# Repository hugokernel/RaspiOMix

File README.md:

RaspiOMix
=========

A RaspberryPi board with 5V tolerance and Grove compatible.

Specifications
--------------

- 4 general 5V tolerant input / output
- 4 analog input, 0-5V, 18 bit resolution (MCP3424)
- 2 digital input via DIP switch
- Real Time Clock with battery backup (DS1307)
- 2 I2C external connector
- 1 serial external connector
- Power input via jack

Python example :

    >>> from raspiomix import Raspiomix
    >>> r = Raspiomix()
    >>> r.readRtc()
    2014-11-12T20:41:26
    >>> print(r.readAdc(0))
    [4.0669732000000005]
    >>>print(r.readAdc((0, 1, 2, 3)))
    [4.066934600000001, 0.010923800000000001, 0.08515160000000001, 0.2866822]

--

Une carte fille pour RaspberryPi avec entrées / sorties tolérantes au 5V et des connecteurs compatible Grove.

Caractéristiques
----------------

- 4 entrées / sorties tolérantes 5V
- 4 entrées analogiques, 0-5V, 18 bits de résolution (MCP3424)
- 2 entrées numériques via DIP switch
- Horloge temps réel avec batterie de sauvegarde (DS1307)
- 2 connecteurs pour I2C
- 1 connecteur pour communication série
- Alimentation via jack

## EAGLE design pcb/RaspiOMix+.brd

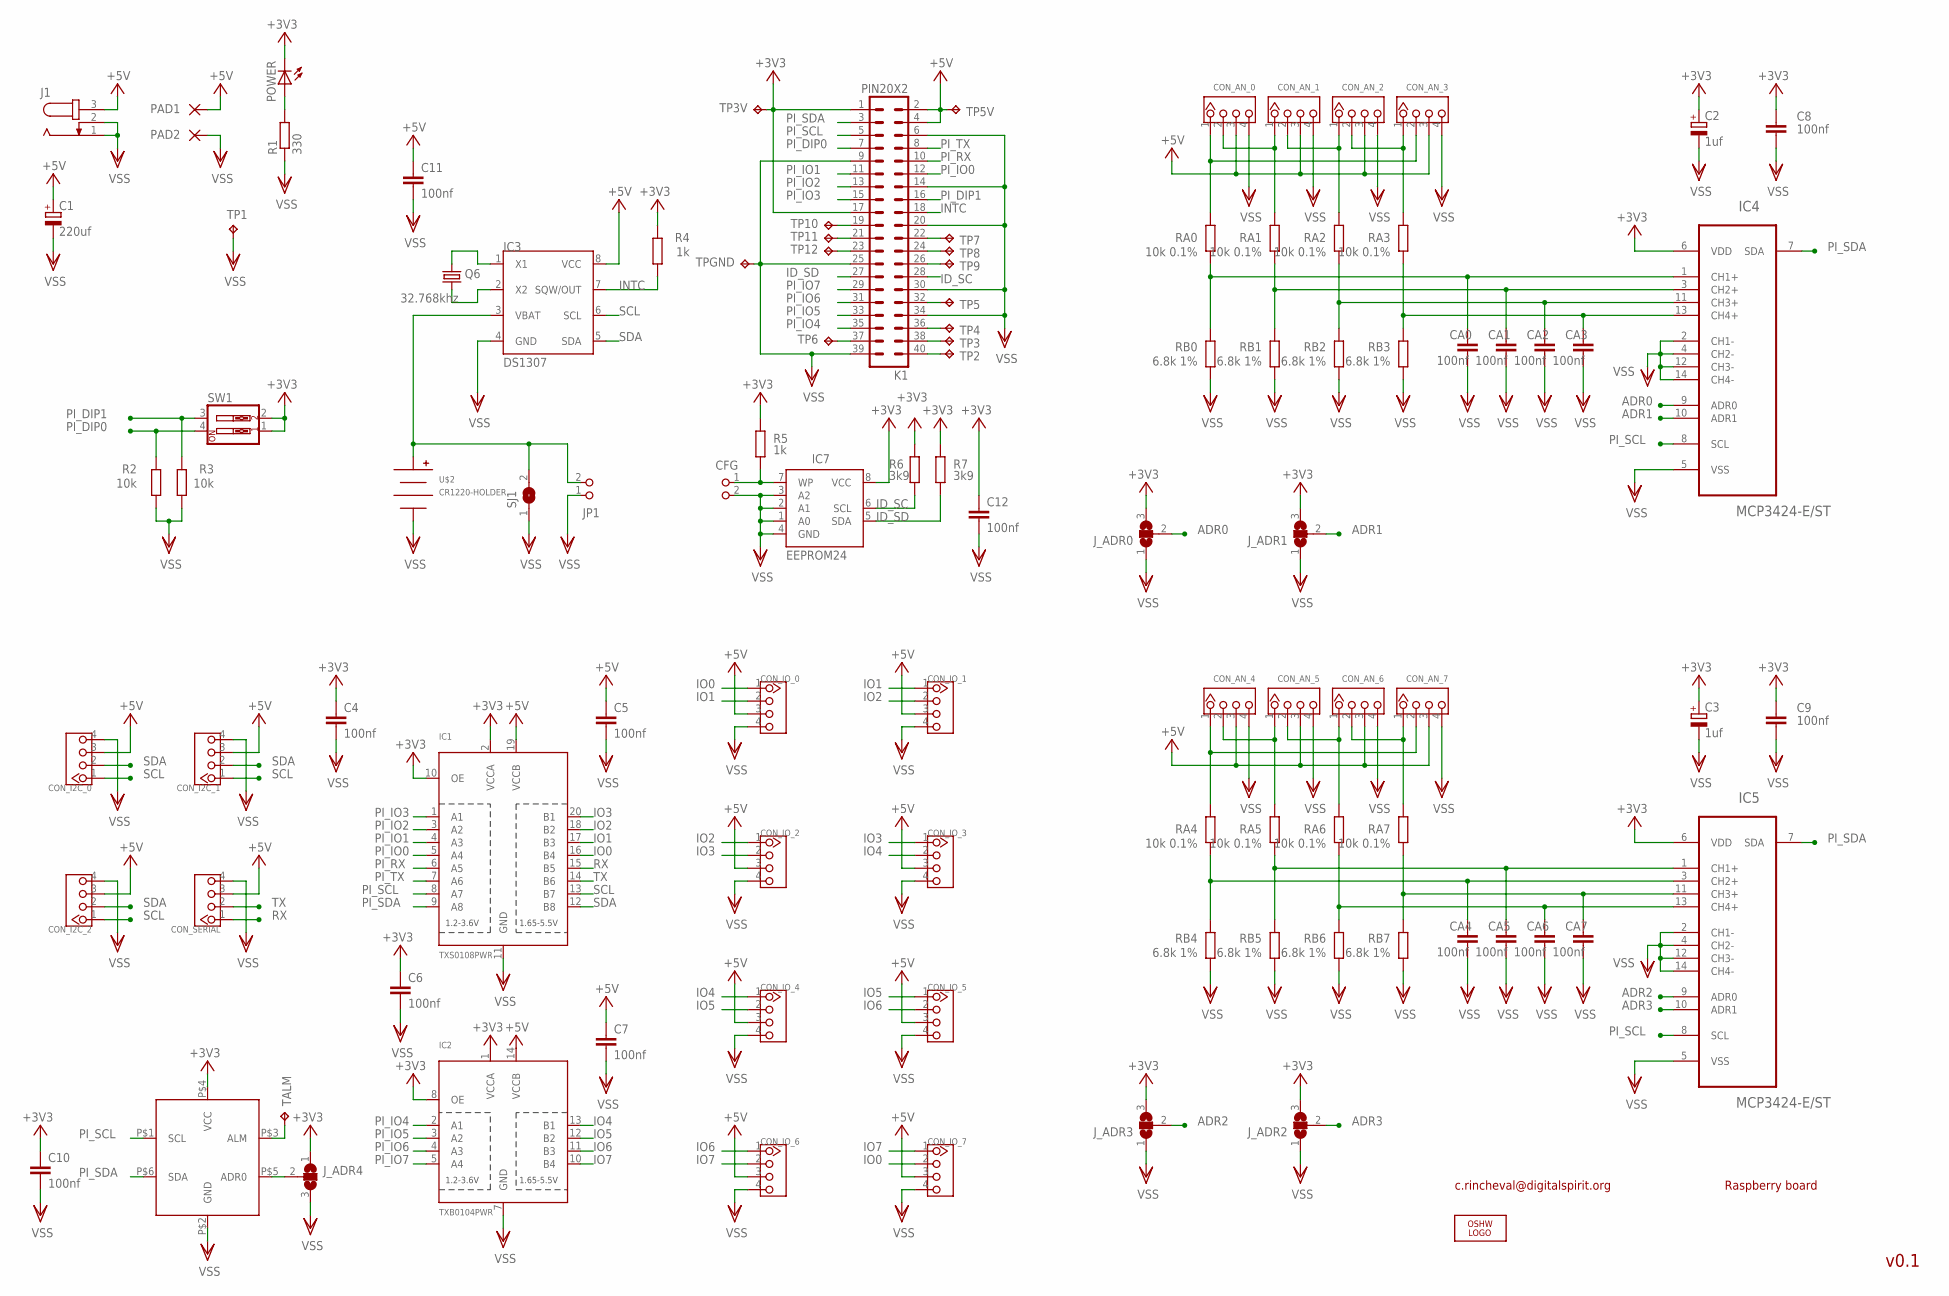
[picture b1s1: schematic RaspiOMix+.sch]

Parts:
C1: 220uf; PANASONIC_D
C2, C3: 1uf; B/3528-21R
C4, C5, C6, C7, C8, C9, C10, C11: 100nf; C0805
C12: 100nf; C0805K
CA0, CA1, CA2, CA3, CA4, CA5, CA6, CA7: 100nf; C0805
CFG: PIN2_100; PIN_W_2
CON_AN_0, CON_AN_1, CON_AN_2, CON_AN_3, CON_AN_4, CON_AN_5, CON_AN_6, CON_AN_7: TWIG-4P-2.0-2.0; 4P-2.0
CON_I2C_0, CON_I2C_1, CON_I2C_2: TWIG-4P-2.0-2.0; 4P-2.0
CON_IO_0, CON_IO_1, CON_IO_2, CON_IO_3, CON_IO_4, CON_IO_5, CON_IO_6, CON_IO_7: TWIG-4P-2.0-2.0; 4P-2.0
CON_SERIAL: TWIG-4P-2.0-2.0; 4P-2.0
IC1: TXS0108PWR; TSSOP20
IC2: TXB0104PWR; TSSOP14
IC3: DS1307; SOIC-8
IC4, IC5: MCP3424-E/ST; SOP65P640X120-14N
IC6: TMP101; SOT23-6
IC7: EEPROM24; SOIC8
J1: JACK-PLUG0; SPC4077
JP1: PIN2_100; PIN_W_2
J_ADR0, J_ADR1, J_ADR2, J_ADR3, J_ADR4: SJ2W; SJ_2
K1: PIN20X2; PIN_20X2
LOGO1: OSHW_LOGO_FILLX0350-NT; OSHW_FILLX350_NOTEXT
PAD1, PAD2: WIREPAD3,17/1,3; 3,17/1,3
POWER: LEDCHIPLED_0805; CHIPLED_0805
Q6: 32.768khz; TC26H
R1: 330; M0805
R2, R3: 10k; M0805
R4: 1k; M0805
R5: 1k; M0805; TOLERANCE 5%
R6, R7: 3k9; M0805; TOLERANCE 5%
RA0, RA1, RA2, RA3, RA4, RA5, RA6, RA7: 10k 0.1%; M0805
RB0, RB1, RB2, RB3, RB4, RB5, RB6, RB7: 6.8k 1%; M0805
SJ1: SJ
SW1: SW_DIP-2; EDG-02
TALM: TPTP12R; TP12R
TP1: TPPAD1-13; P1-13
TP2, TP3, TP3V, TP4, TP5, TP5V, TP6, TP7, TP8, TP9, TP10, TP11, TP12: TPTP12R; TP12R
TPGND: TPTP12R; TP12R
U$2: CR1220-HOLDER; HARWIN-CR1220

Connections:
+3V3: C2.+, C3.+, C4.1, C6.1, C8.2, C9.2, C10.1, C12.1, IC1.2 (VCCA), IC1.10 (OE), IC2.1 (VCCA), IC2.8 (OE), IC4.6 (VDD), IC5.6 (VDD), IC6.P$4 (VCC), IC7.8 (VCC), J_ADR0.3, J_ADR1.3, J_ADR2.3, J_ADR3.3, J_ADR4.1, K1.1, K1.17, POWER.C, R4.2, R5.2, R6.2, R7.2, SW1.1, SW1.2, TP3V.TP
+5V: C1.+, C5.1, C7.1, C11.1, CON_AN_0.3, CON_AN_1.3, CON_AN_2.3, CON_AN_3.3, CON_AN_4.3, CON_AN_5.3, CON_AN_6.3, CON_AN_7.3, CON_I2C_0.3, CON_I2C_1.3, CON_I2C_2.3, CON_IO_0.3, CON_IO_1.3, CON_IO_2.3, CON_IO_3.3, CON_IO_4.3, CON_IO_5.3, CON_IO_6.3, CON_IO_7.3, CON_SERIAL.3, IC1.19 (VCCB), IC2.14 (VCCB), IC3.8 (VCC), J1.3, K1.2, K1.4, PAD1.1, TP5V.TP
ADR0: IC4.9 (ADR0), J_ADR0.2
ADR1: IC4.10 (ADR1), J_ADR1.2
ADR2: IC5.9 (ADR0), J_ADR3.2
ADR3: IC5.10 (ADR1), J_ADR2.2
AN0: CON_AN_0.1, CON_AN_3.2, RA0.2
AN1: CON_AN_0.2, CON_AN_1.1, RA1.2
AN2: CON_AN_1.2, CON_AN_2.1, RA2.2
AN3: CON_AN_2.2, CON_AN_3.1, RA3.2
AN4: CON_AN_4.1, CON_AN_7.2, RA4.2
AN5: CON_AN_4.2, CON_AN_5.1, RA5.2
AN6: CON_AN_5.2, CON_AN_6.1, RA6.2
AN7: CON_AN_6.2, CON_AN_7.1, RA7.2
ID_SC: IC7.6 (SCL), K1.28, R6.1
ID_SD: IC7.5 (SDA), K1.27, R7.1
INTC: IC3.7 (SQW/OUT), K1.18, R4.1
IO0: CON_IO_0.1, CON_IO_7.2, IC1.16 (B4)
IO1: CON_IO_0.2, CON_IO_1.1, IC1.17 (B3)
IO2: CON_IO_1.2, CON_IO_2.1, IC1.18 (B2)
IO3: CON_IO_2.2, CON_IO_3.1, IC1.20 (B1)
IO4: CON_IO_3.2, CON_IO_4.1, IC2.13 (B1)
IO5: CON_IO_4.2, CON_IO_5.1, IC2.12 (B2)
IO6: CON_IO_5.2, CON_IO_6.1, IC2.11 (B3)
IO7: CON_IO_6.2, CON_IO_7.1, IC2.10 (B4)
unnamed: K1.40, TP2.TP
unnamed: K1.38, TP3.TP
unnamed: CFG.1, IC7.7 (WP), R5.1
unnamed: CA3.1, IC4.13 (CH4+), RA3.1, RB3.2
unnamed: CA2.1, IC4.11 (CH3+), RA2.1, RB2.2
unnamed: CA1.1, IC4.3 (CH2+), RA1.1, RB1.2
unnamed: CA0.1, IC4.1 (CH1+), RA0.1, RB0.2
unnamed: CA7.1, IC5.11 (CH3+), RA7.1, RB7.2
unnamed: CA6.1, IC5.13 (CH4+), RA6.1, RB6.2
unnamed: CA5.1, IC5.1 (CH1+), RA5.1, RB5.2
unnamed: CA4.1, IC5.3 (CH2+), RA4.1, RB4.2
unnamed: K1.36, TP4.TP
unnamed: K1.32, TP5.TP
unnamed: K1.37, TP6.TP
unnamed: K1.22, TP7.TP
unnamed: K1.24, TP8.TP
unnamed: K1.26, TP9.TP
unnamed: K1.19, TP10.TP
unnamed: K1.21, TP11.TP
unnamed: K1.23, TP12.TP
unnamed: IC6.P$5 (ADR0), J_ADR4.2
unnamed: IC6.P$3 (ALM), TALM.TP
unnamed: IC3.1 (X1), Q6.1
unnamed: IC3.2 (X2), Q6.2
unnamed: POWER.A, R1.2
unnamed: IC3.3 (VBAT), JP1.2, SJ1.2, U$2.POS
PI_DIP0: K1.7, R2.2, SW1.4
PI_DIP1: K1.16, R3.2, SW1.3
PI_IO0: IC1.5 (A4), K1.12
PI_IO1: IC1.4 (A3), K1.11
PI_IO2: IC1.3 (A2), K1.13
PI_IO3: IC1.1 (A1), K1.15
PI_IO4: IC2.2 (A1), K1.35
PI_IO5: IC2.3 (A2), K1.33
PI_IO6: IC2.4 (A3), K1.31
PI_IO7: IC2.5 (A4), K1.29
PI_RX: IC1.6 (A5), K1.10
PI_SCL: IC1.8 (A7), IC4.8 (SCL), IC5.8 (SCL), IC6.P$1 (SCL), K1.5
PI_SDA: IC1.9 (A8), IC4.7 (SDA), IC5.7 (SDA), IC6.P$6 (SDA), K1.3
PI_TX: IC1.7 (A6), K1.8
RX: CON_SERIAL.1, IC1.15 (B5)
SCL: CON_I2C_0.1, CON_I2C_1.1, CON_I2C_2.1, IC1.13 (B7), IC3.6 (SCL)
SDA: CON_I2C_0.2, CON_I2C_1.2, CON_I2C_2.2, IC1.12 (B8), IC3.5 (SDA)
TX: CON_SERIAL.2, IC1.14 (B6)
VSS: C1.-, C2.-, C3.-, C4.2, C5.2, C6.2, C7.2, C8.1, C9.1, C10.2, C11.2, C12.2, CA0.2, CA1.2, CA2.2, CA3.2, CA4.2, CA5.2, CA6.2, CA7.2, CFG.2, CON_AN_0.4, CON_AN_1.4, CON_AN_2.4, CON_AN_3.4, CON_AN_4.4, CON_AN_5.4, CON_AN_6.4, CON_AN_7.4, CON_I2C_0.4, CON_I2C_1.4, CON_I2C_2.4, CON_IO_0.4, CON_IO_1.4, CON_IO_2.4, CON_IO_3.4, CON_IO_4.4, CON_IO_5.4, CON_IO_6.4, CON_IO_7.4, CON_SERIAL.4, IC1.11 (GND), IC2.7 (GND), IC3.4 (GND), IC4.2 (CH1-), IC4.4 (CH2-), IC4.5 (VSS), IC4.12 (CH3-), IC4.14 (CH4-), IC5.2 (CH1-), IC5.4 (CH2-), IC5.5 (VSS), IC5.12 (CH3-), IC5.14 (CH4-), IC6.P$2 (GND), IC7.1 (A0), IC7.2 (A1), IC7.3 (A2), IC7.4 (GND), J1.1, J1.2, JP1.1, J_ADR0.1, J_ADR1.1, J_ADR2.1, J_ADR3.1, J_ADR4.3, K1.6, K1.9, K1.14, K1.20, K1.25, K1.30, K1.34, K1.39, PAD2.1, R1.1, R2.1, R3.1, RB0.1, RB1.1, RB2.1, RB3.1, RB4.1, RB5.1, RB6.1, RB7.1, SJ1.1, TP1.TP, TPGND.TP, U$2.NEG

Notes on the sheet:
v0.1
c.rincheval@digitalspirit.org
Raspberry board

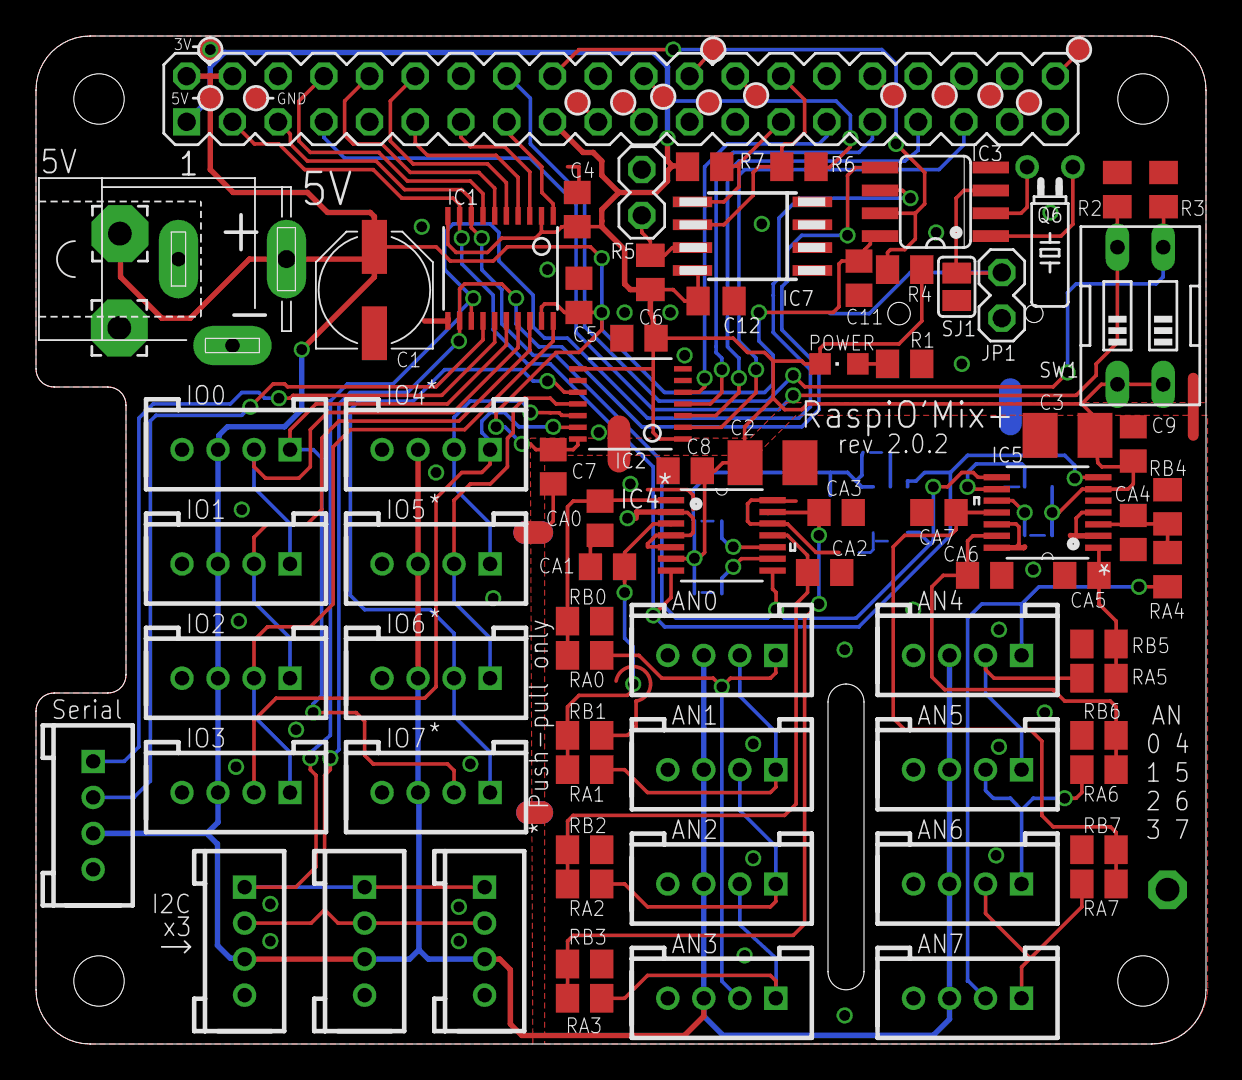
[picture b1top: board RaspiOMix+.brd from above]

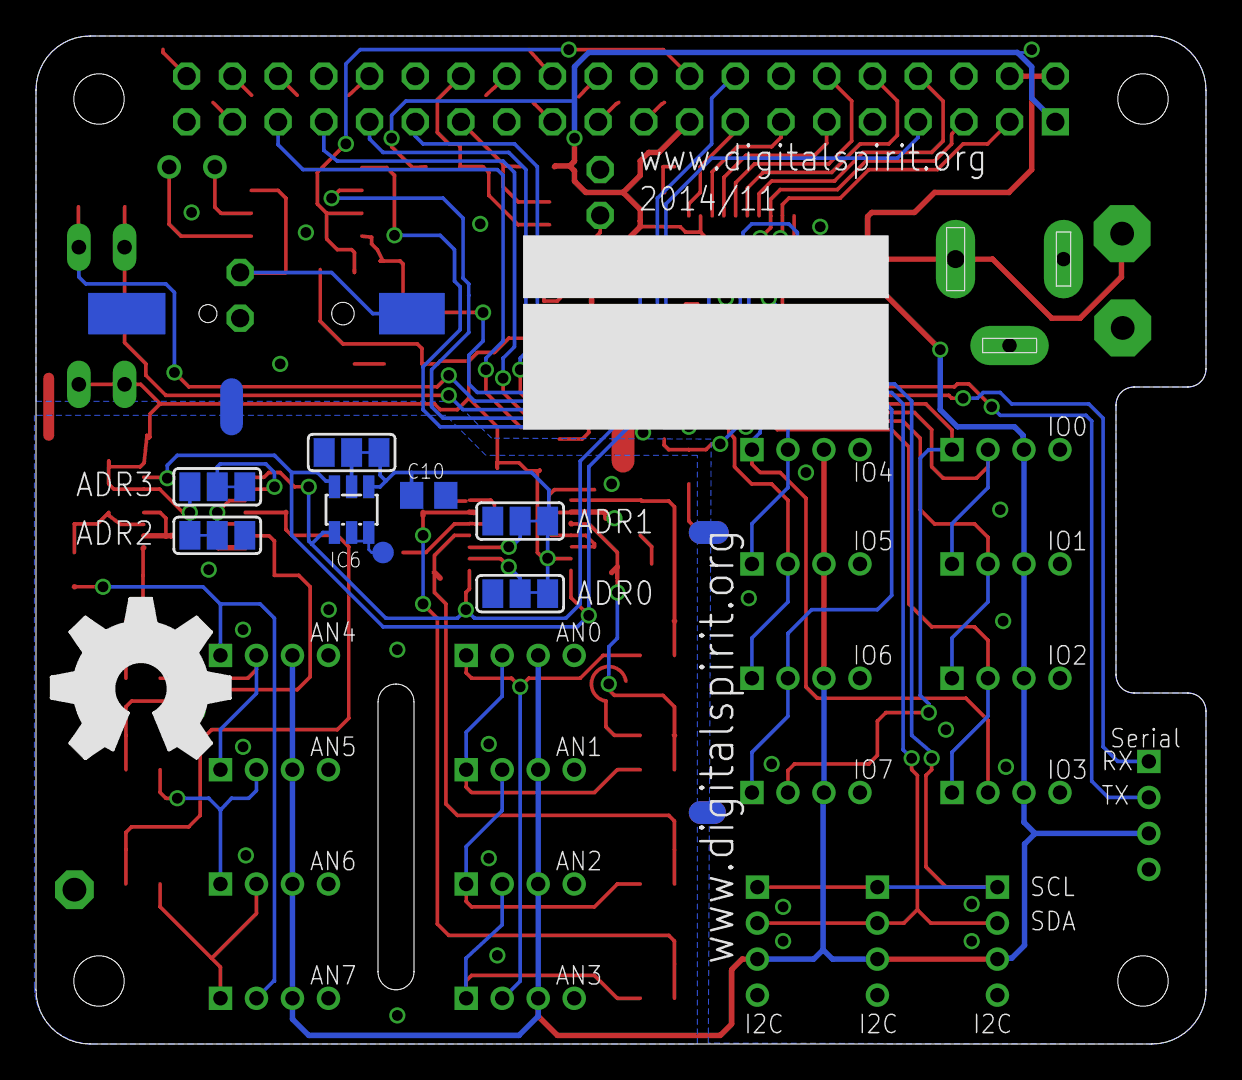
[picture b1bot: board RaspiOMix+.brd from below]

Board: 2 copper layers, 65.0 x 56.0 mm, 103 parts (10 on the bottom side), 70 nets.

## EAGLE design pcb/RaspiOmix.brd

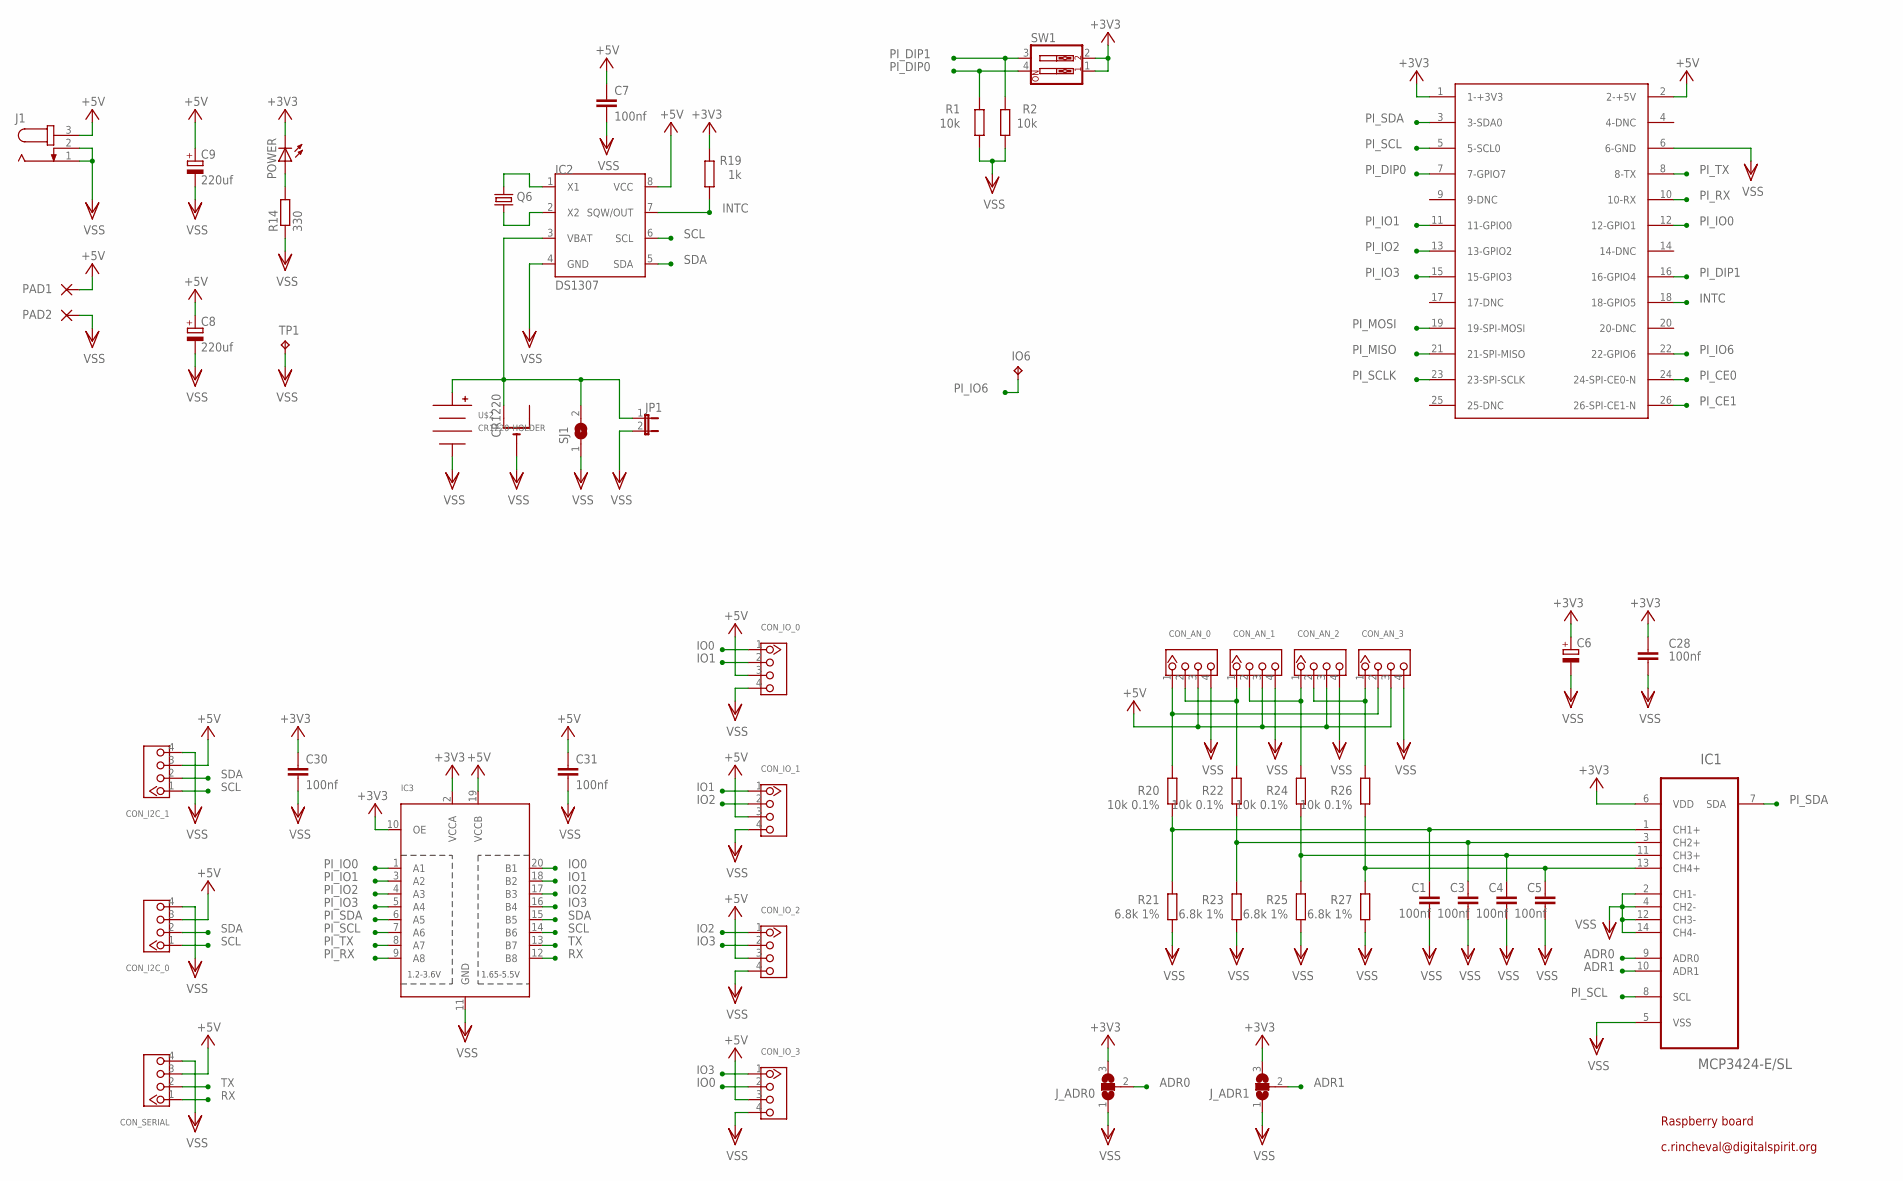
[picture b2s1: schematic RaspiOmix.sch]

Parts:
C1, C3, C4, C5, C7, C28, C30, C31: 100nf; C0805
C6: CPOL-EUB/3528-21R; B/3528-21R
C8, C9: 220uf; PANASONIC_D
CON_AN_0, CON_AN_1, CON_AN_2, CON_AN_3: TWIG-4P-2.0'90D'; 4P-2.0-90D
CON_I2C_0, CON_I2C_1: TWIG-4P-2.0'90D'; 4P-2.0-90D
CON_IO_0, CON_IO_1, CON_IO_2, CON_IO_3: TWIG-4P-2.0'90D'; 4P-2.0-90D
CON_SERIAL: TWIG-4P-2.0'90D'; 4P-2.0-90D
CR1220: CR1220THM; CR1220-THM
IC1: MCP3424-E/SL; SOIC-14
IC2: DS1307; SOIC-8
IC3: TXB0108PWR; TSSOP20
IO6: TPPAD1-13; P1-13
J1: JACK-PLUG0; SPC4077
JP1: JP1E; JP1
J_ADR0, J_ADR1: SJ2W; SJ_2
PAD1, PAD2: WIREPAD3,17/1,3; 3,17/1,3
POWER: LEDCHIPLED_0805; CHIPLED_0805
Q6: CRYSTALTC26H; TC26H
R1, R2: 10k; M0805
R14: 330; M0805
R19: 1k; M0805
R20, R22, R24, R26: 10k 0.1%; M0805
R21, R23, R25, R27: 6.8k 1%; M0805
SJ1: SJ
SW1: SW_DIP-2; EDG-02
TP1: TPPAD1-13; P1-13
U$2: CR1220-HOLDER; HARWIN-CR1220
U$3: RASPBERRY-PILIGHT-HOLE; RASPBERRY-PI-LIGHT-HOLE

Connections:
+3V3: C6.+, C28.2, C30.1, IC1.6 (VDD), IC3.2 (VCCA), IC3.10 (OE), J_ADR0.3, J_ADR1.3, POWER.C, R19.2, SW1.1, SW1.2, U$3.1 (1-+3V3)
+5V: C7.1, C8.+, C9.+, C31.1, CON_AN_0.3, CON_AN_1.3, CON_AN_2.3, CON_AN_3.3, CON_I2C_0.3, CON_I2C_1.3, CON_IO_0.3, CON_IO_1.3, CON_IO_2.3, CON_IO_3.3, CON_SERIAL.3, IC2.8 (VCC), IC3.19 (VCCB), J1.3, PAD1.1, U$3.2 (2-+5V)
ADR0: IC1.9 (ADR0), J_ADR0.2
ADR1: IC1.10 (ADR1), J_ADR1.2
AN0: CON_AN_0.1, CON_AN_3.2, R20.2
AN1: CON_AN_0.2, CON_AN_1.1, R22.2
AN2: CON_AN_1.2, CON_AN_2.1, R24.2
AN3: CON_AN_2.2, CON_AN_3.1, R26.2
INTC: IC2.7 (SQW/OUT), R19.1, U$3.18 (18-GPIO5)
IO0: CON_IO_0.1, CON_IO_3.2, IC3.20 (B1)
IO1: CON_IO_0.2, CON_IO_1.1, IC3.18 (B2)
IO2: CON_IO_1.2, CON_IO_2.1, IC3.17 (B3)
IO3: CON_IO_2.2, CON_IO_3.1, IC3.16 (B4)
unnamed: C5.1, IC1.13 (CH4+), R26.1, R27.2
unnamed: C4.1, IC1.11 (CH3+), R24.1, R25.2
unnamed: C3.1, IC1.3 (CH2+), R22.1, R23.2
unnamed: C1.1, IC1.1 (CH1+), R20.1, R21.2
unnamed: IC2.1 (X1), Q6.1
unnamed: IC2.2 (X2), Q6.2
unnamed: POWER.A, R14.2
unnamed: CR1220.+1 (+), IC2.3 (VBAT), JP1.1, SJ1.2, U$2.POS
PI_CE0: U$3.24 (24-SPI-CE0-N)
PI_CE1: U$3.26 (26-SPI-CE1-N)
PI_DIP0: R1.2, SW1.4, U$3.7 (7-GPIO7)
PI_DIP1: R2.2, SW1.3, U$3.16 (16-GPIO4)
PI_IO0: IC3.1 (A1), U$3.12 (12-GPIO1)
PI_IO1: IC3.3 (A2), U$3.11 (11-GPIO0)
PI_IO2: IC3.4 (A3), U$3.13 (13-GPIO2)
PI_IO3: IC3.5 (A4), U$3.15 (15-GPIO3)
PI_IO6: IO6.TP, U$3.22 (22-GPIO6)
PI_MISO: U$3.21 (21-SPI-MISO)
PI_MOSI: U$3.19 (19-SPI-MOSI)
PI_RX: IC3.9 (A8), U$3.10 (10-RX)
PI_SCL: IC1.8 (SCL), IC3.7 (A6), U$3.5 (5-SCL0)
PI_SCLK: U$3.23 (23-SPI-SCLK)
PI_SDA: IC1.7 (SDA), IC3.6 (A5), U$3.3 (3-SDA0)
PI_TX: IC3.8 (A7), U$3.8 (8-TX)
RX: CON_SERIAL.1, IC3.12 (B8)
SCL: CON_I2C_0.1, CON_I2C_1.1, IC2.6 (SCL), IC3.14 (B6)
SDA: CON_I2C_0.2, CON_I2C_1.2, IC2.5 (SDA), IC3.15 (B5)
TX: CON_SERIAL.2, IC3.13 (B7)
VSS: C1.2, C3.2, C4.2, C5.2, C6.-, C7.2, C8.-, C9.-, C28.1, C30.2, C31.2, CON_AN_0.4, CON_AN_1.4, CON_AN_2.4, CON_AN_3.4, CON_I2C_0.4, CON_I2C_1.4, CON_IO_0.4, CON_IO_1.4, CON_IO_2.4, CON_IO_3.4, CON_SERIAL.4, CR1220.-, IC1.2 (CH1-), IC1.4 (CH2-), IC1.5 (VSS), IC1.12 (CH3-), IC1.14 (CH4-), IC2.4 (GND), IC3.11 (GND), J1.1, J1.2, JP1.2, J_ADR0.1, J_ADR1.1, PAD2.1, R1.1, R2.1, R14.1, R21.1, R23.1, R25.1, R27.1, SJ1.1, TP1.TP, U$2.NEG, U$3.6 (6-GND)

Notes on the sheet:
c.rincheval@digitalspirit.org
Raspberry board

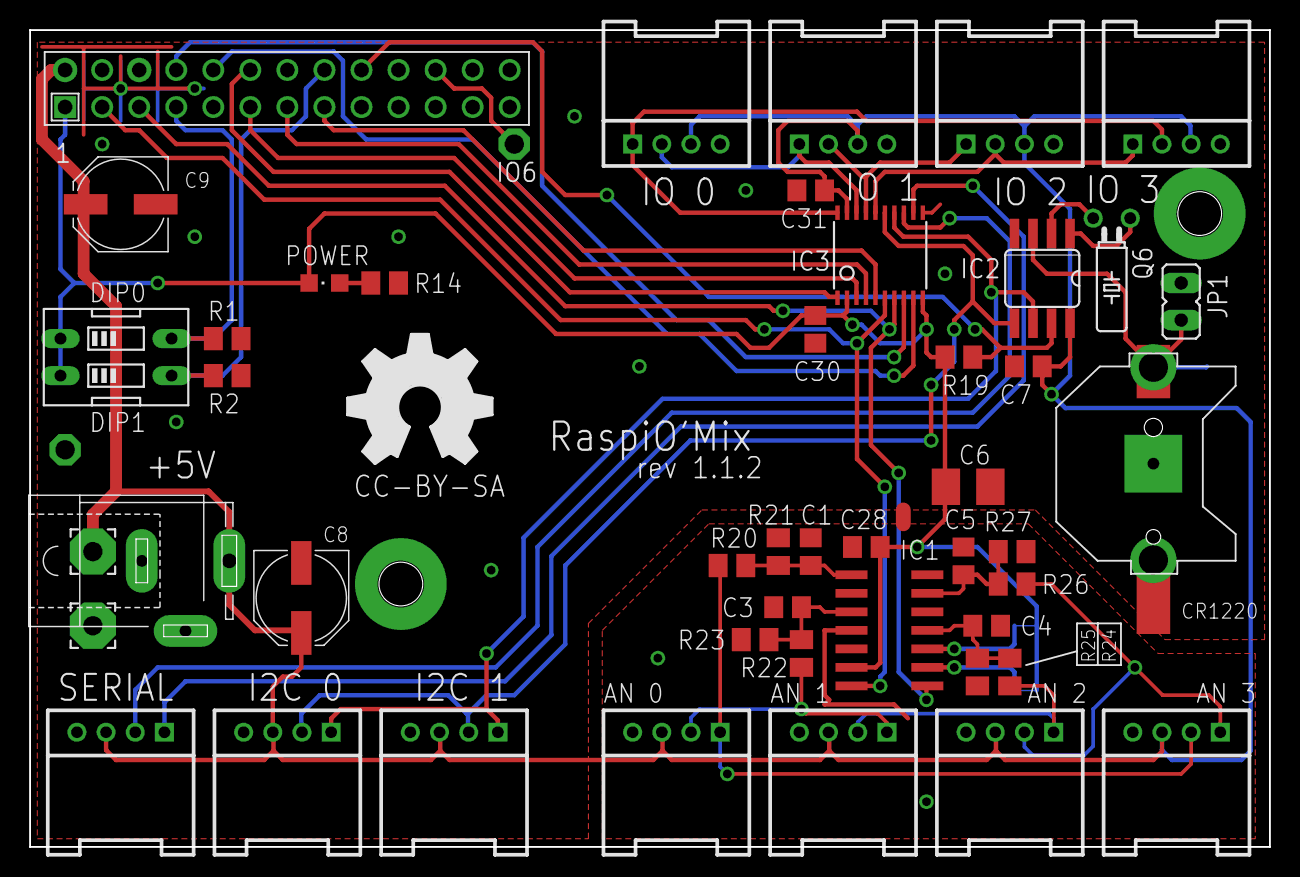
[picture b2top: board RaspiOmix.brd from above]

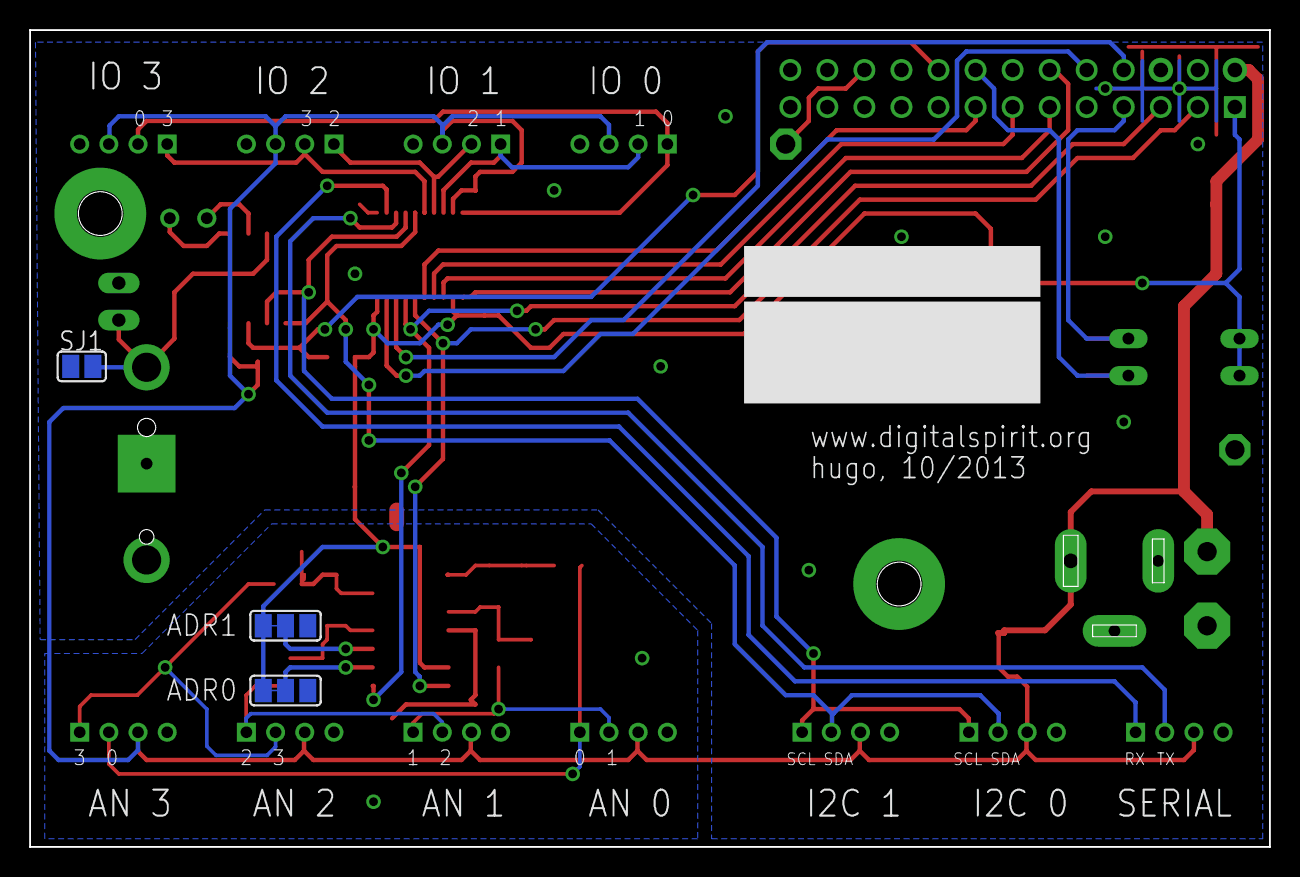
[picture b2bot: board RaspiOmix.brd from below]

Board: 2 copper layers, 85.0 x 56.0 mm, 53 parts (3 on the bottom side), 37 nets.

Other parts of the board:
U$1: OSHW_FILLX350_NOTEXT

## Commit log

2013-06-13 Clear, text, license
2013-06-13 Clean + gitignore
2013-06-14 Small modif !
2013-06-14 Added C6
2013-06-14 Screen
2013-06-24 Version avec Mosfet
2013-06-24 Version 1.0.0
2013-06-24 Version 1.0.1
    Hole size modification
2013-07-12 Source code
2013-07-17 Code
2013-07-17 Clean
2013-07-17 Test
2013-07-22 PCB 1.0.8
    - Inverse grove connector
    - Hole connector linked to VSS
2013-07-28 Move C9 label
2013-07-28 Petite modif
2013-09-13 Adds simple tests scripts in python and ruby
    curses-less python analog test script
    Ruby analog test script
    Boths scripts uses the i2c kenel interface.
2013-09-13 Fixes i2c address constant
    Changed ADC_I2C_ADDRESS to I2C_ADC_ADDRESS as per raspiomix.py
2013-10-03 PCB 1.1.1
2013-11-02 Source modification
2014-11-12 New RaspiO'Mix+ hat
    Schema + PCB in progress…
2014-11-12 New Python lib
    Embed i2c methods (adc, rtc) in lib
2014-11-12 Python example
2014-11-12 Correction
2014-11-13 Routage
2014-11-19 Routage PCB
2014-12-02 RaspiO'Mix rev 1.0.0
2015-03-02 RaspiO'Mix+
    Modif
2015-03-06 RaspiO'Mix+ -> Pcb 2.0.0
    New RaspiO’Mix+ pcbs version is 2.0.0.
2015-03-06 Version 1.1.1 modification
2015-04-03 Test correction
2015-05-19 Misc
2015-05-19 Allow single channel read
2015-05-29 Misc
    Added Python example
    Added serial line in Python library
2017-07-05 PCB Version 2.0.2

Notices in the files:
pcb/RaspiOmix.brd:
CC-BY-SA
